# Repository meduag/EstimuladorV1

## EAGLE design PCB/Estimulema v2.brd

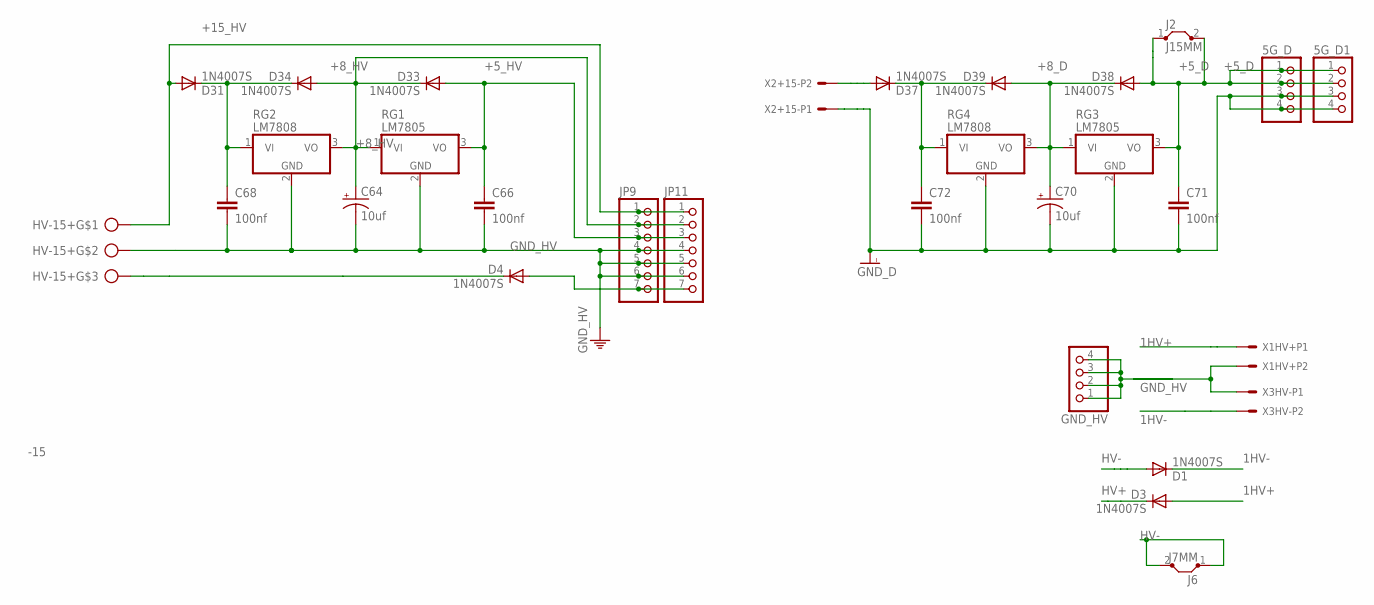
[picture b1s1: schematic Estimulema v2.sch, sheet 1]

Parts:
5G_D, 5G_D1: PINHD-1X4; 1X04
C64, C70: 10uf; E2-5
C66, C68, C71, C72: 100nf; C025-025X050
D1, D3, D4, D31, D33, D34, D37, D38, D39: 1N4007S; RESM4226X229
GND_HV: PINHD-1X4; 1X04
HV-15+: CONECTOR_3_PTR500; PTR_AK300/3
J2: J15MM; 15
J6: J7MM; 07
JP9, JP11: PINHD-1X7; 1X07
RG1, RG3: LM7805; TO220V
RG2, RG4: LM7808; TO220V
X1HV+, X2+15-, X3HV-: CONECTOR_5.08; CONECTOR_X2_5.08

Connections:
1HV+: D3.AN (A), X1HV+.1
1HV-: D1.CA (C), X3HV-.2
+5_D: 5G_D.1, 5G_D.2, 5G_D1.1, 5G_D1.2, C71.1, D38.AN (A), J2.1, J2.2, RG3.3 (VO); also elsewhere on the board
+5_HV: C66.1, D33.AN (A), JP9.3, JP11.3, RG1.3 (VO); also elsewhere on the board
+8_D: C70.+, D38.CA (C), D39.AN (A), RG3.1 (VI), RG4.3 (VO)
+8_HV: C64.+, D33.CA (C), D34.AN (A), JP9.2, JP11.2, RG1.1 (VI), RG2.3 (VO)
+15_HV: D31.AN (A), HV-15+.1, JP9.1, JP11.1; also elsewhere on the board
-15: D4.CA (C), HV-15+.3
-15_HV: D4.AN (A), JP9.7, JP11.7; also elsewhere on the board
GND_D: 5G_D.3, 5G_D.4, 5G_D1.3, 5G_D1.4, C70.-, C71.2, C72.2, RG3.2 (GND), RG4.2 (GND), X2+15-.1; also elsewhere on the board
GND_HV: C64.-, C66.2, C68.2, GND_HV.1, GND_HV.2, GND_HV.3, GND_HV.4, HV-15+.2, JP9.4, JP9.5, JP9.6, JP11.4, JP11.5, JP11.6, RG1.2 (GND), RG2.2 (GND), X1HV+.2, X3HV-.1; also elsewhere on the board
HV+: D3.CA (C); also elsewhere on the board
HV-: D1.AN (A), J6.1, J6.2; also elsewhere on the board
unnamed: D37.AN (A), X2+15-.2
unnamed: C68.1, D31.CA (C), D34.CA (C), RG2.1 (VI)
unnamed: C72.1, D37.CA (C), D39.CA (C), RG4.1 (VI)

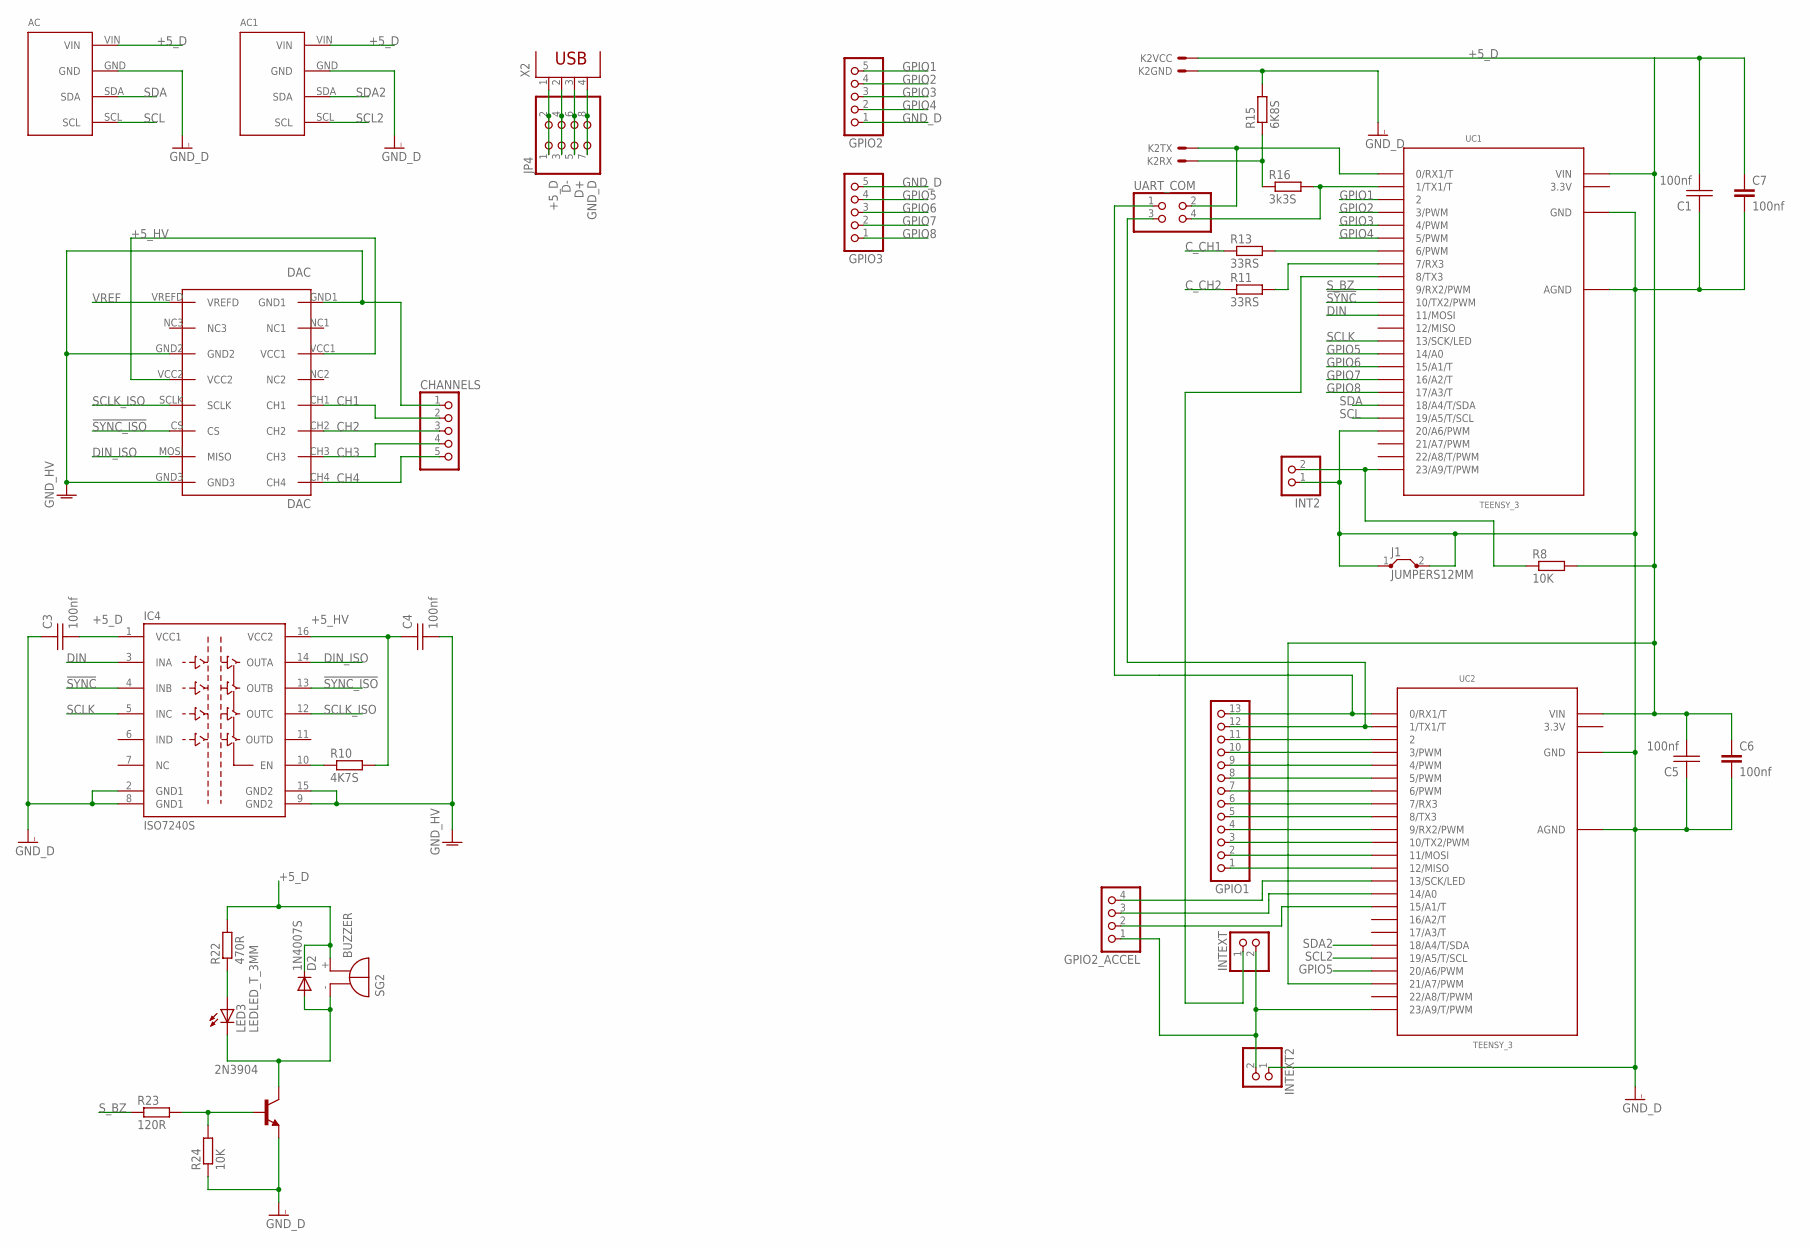
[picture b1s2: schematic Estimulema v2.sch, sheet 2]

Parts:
2N3904: 29-NPN-TO92-EBC; TO92-EBC
AC: CONECTOR_ACELEROMETRO_MPU6050CONECTOR_MPU6050; MPU6050
AC1: MPU6050
C1, C3, C4, C5: 100nf; CAP_CER_SMD-0805
C6, C7: 100nf; C025-025X050
CHANNELS: PINHD-1X5; 1X05
D2: 1N4007S; RESM4226X229
DAC: DAC; DACMOD_P
GPIO1: PINHD-1X13; 1X13
GPIO2, GPIO3: PINHD-1X5; 1X05
GPIO2_ACCEL: PINHD-1X4; 1X04
IC4: ISO7240S; SO-16DW
INT2: PINHD-1X2; 1X02
INTEXT, INTEXT2: PINHD-1X2; 1X02
J1: JUMPERS12MM; 12
JP4: PINHD-2X4; 2X04
K2: HC-06; CONECTOR_BTHC-06
LED3: LEDLED_T_3MM; LED3MM
R8, R24: 10K; RESISTENCIA_0805
R10: 4K7S; RESISTENCIA_0805
R11, R13: 33RS; RESISTENCIA_0805
R15: 6K8S; RESISTENCIA_0805
R16: 3k3S; RESISTENCIA_0805
R22: 470R; RESISTENCIA_0805
R23: 120R; RESISTENCIA_0805
SG2: BUZZER
UART_COM: PINHD-2X2; 2X02
UC1, UC2: TEENSY_3; TEENSY_3.0-3.2_DIL
X2: PN61729

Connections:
3.3V: UC1.3.3V, UC2.3.3V
!SYNC: IC4.4 (INB), UC1.10 (10/TX2/PWM)
!SYNC_ISO: DAC.CS, IC4.13 (OUTB)
+5_D: AC.VIN, AC1.VIN, C1.2, C3.2, C5.2, C6.1, C7.1, D2.CA (C), IC4.1 (VCC1), JP4.1, JP4.2, K2.1, R8.2, R22.2, SG2.+ (-), UC1.VIN, UC2.21/A7 (21/A7/PWM), UC2.VIN, X2.1; also elsewhere on the board
+5_HV: C4.1, DAC.VCC1, DAC.VCC2, IC4.16 (VCC2), R10.2; also elsewhere on the board
CH1: CHANNELS.2, DAC.CH1; also elsewhere on the board
CH2: CHANNELS.3, DAC.CH2; also elsewhere on the board
CH3: CHANNELS.4, DAC.CH3
CH4: CHANNELS.5, DAC.CH4
C_15D: GPIO1.11, UC2.2
C_CH1: R13.1; also elsewhere on the board
C_CH2: R11.1; also elsewhere on the board
D+: JP4.5, JP4.6, X2.3
D-: JP4.3, JP4.4, X2.2
DIN: IC4.3 (INA), UC1.11 (11/MOSI)
DIN_ISO: DAC.MOSI (MISO), IC4.14 (OUTA)
GND_D: 2N3904.E, AC.GND, AC1.GND, C1.1, C3.1, C5.1, C6.2, C7.2, GPIO2.1, GPIO3.5, IC4.2 (GND1), IC4.8 (GND1), INT2.1, INTEXT2.1, J1.1, J1.2, JP4.7, JP4.8, K2.2, R15.2, R24.1, UC1.20/A6 (20/A6/PWM), UC1.AGND, UC1.GND, UC2.AGND, UC2.GND, X2.4; also elsewhere on the board
GND_HV: C4.2, CHANNELS.1, DAC.GND1, DAC.GND2, DAC.GND3, IC4.9 (GND2), IC4.15 (GND2); also elsewhere on the board
GPIO1: GPIO2.5, UC1.2
GPIO2: GPIO2.4, UC1.3 (3/PWM)
GPIO3: GPIO2.3, UC1.4 (4/PWM)
GPIO4: GPIO2.2, UC1.5 (5/PWM)
GPIO5: GPIO3.4, UC1.14/A0, UC2.20/A6 (20/A6/PWM)
GPIO6: GPIO3.3, UC1.15/A1 (15/A1/T)
GPIO7: GPIO3.2, UC1.16/A2 (16/A2/T)
GPIO8: GPIO3.1, UC1.17/A3 (17/A3/T)
unnamed: GPIO2_ACCEL.1, INTEXT.2, INTEXT2.2, UC2.23/A9 (23/A9/T/PWM)
unnamed: INTEXT.1, UC1.8 (8/TX3)
unnamed: GPIO1.13, UART_COM.1, UC2.0 (0/RX1/T)
unnamed: GPIO1.12, UART_COM.3, UC2.1 (1/TX1/T)
unnamed: GPIO1.10, UC2.3 (3/PWM)
unnamed: GPIO1.9, UC2.4 (4/PWM)
unnamed: GPIO1.8, UC2.5 (5/PWM)
unnamed: GPIO1.7, UC2.6 (6/PWM)
unnamed: GPIO1.6, UC2.7 (7/RX3)
unnamed: GPIO1.5, UC2.8 (8/TX3)
unnamed: GPIO1.4, UC2.9 (9/RX2/PWM)
unnamed: GPIO1.3, UC2.10 (10/TX2/PWM)
unnamed: GPIO1.2, UC2.11 (11/MOSI)
unnamed: GPIO1.1, UC2.12 (12/MISO)
unnamed: R16.2, UART_COM.4, UC1.1 (1/TX1/T)
unnamed: GPIO2_ACCEL.4, UC2.13 (13/SCK/LED)
unnamed: K2.3, UART_COM.2, UC1.0 (0/RX1/T)
unnamed: GPIO2_ACCEL.3, UC2.14/A0
unnamed: GPIO2_ACCEL.2, UC2.15/A1 (15/A1/T)
unnamed: IC4.10 (EN), R10.1
unnamed: K2.4, R15.1, R16.1
unnamed: LED3.A, R22.1
unnamed: 2N3904.C, D2.AN (A), LED3.K (C), SG2.- (+)
unnamed: 2N3904.B, R23.2, R24.2
unnamed: INT2.2, R8.1, UC1.23/A9 (23/A9/T/PWM)
RL1: R13.2, UC1.6 (6/PWM)
RL2: R11.2, UC1.7 (7/RX3)
SCL: AC.SCL, UC1.19/A5 (19/A5/T/SCL)
SCL2: AC1.SCL, UC2.19/A5 (19/A5/T/SCL)
SCLK: IC4.5 (INC), UC1.13 (13/SCK/LED)
SCLK_ISO: DAC.SCLK, IC4.12 (OUTC)
SDA: AC.SDA, UC1.18/A4 (18/A4/T/SDA)
SDA2: AC1.SDA, UC2.18/A4 (18/A4/T/SDA)
S_BZ: R23.1, UC1.9 (9/RX2/PWM)
VREF: DAC.VREFD; also elsewhere on the board

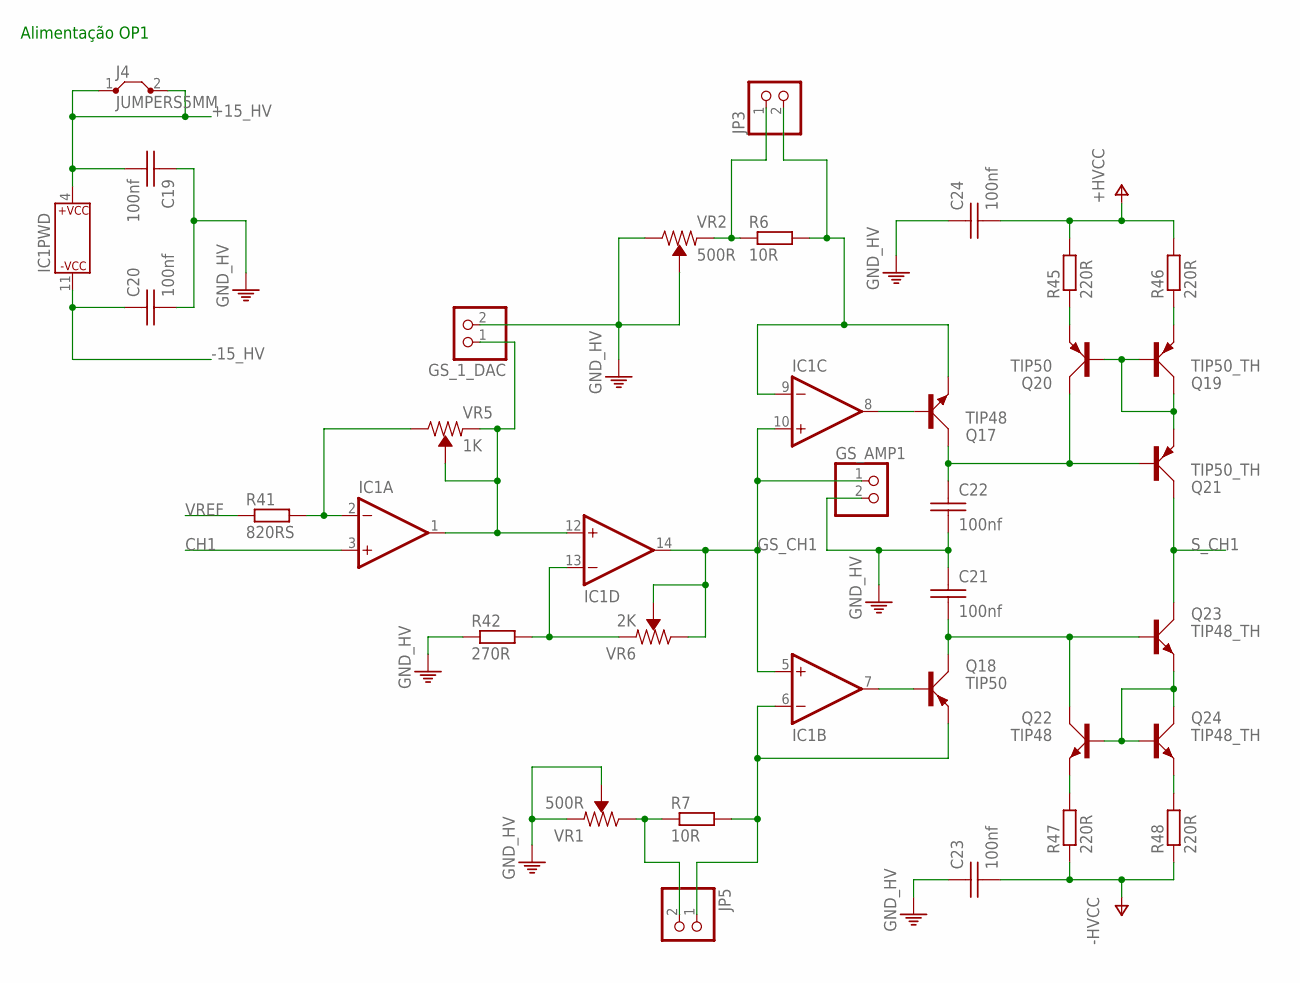
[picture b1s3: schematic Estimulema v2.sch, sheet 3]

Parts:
C19, C20: 100nf; CAP_CER_SMD-0805
C21, C22: 100nf; CAP_CER_2,54-5X5
C23, C24: 100nf; CAP_CER_16X7
GS_1_DAC: PINHD-1X2; 1X02
GS_AMP1: PINHD-1X2; 1X02
IC1: TL084DIL143D; DIL14
J4: JUMPERS5MM; 05
JP3, JP5: PINHD-1X2; 1X02
Q17, Q22: TIP48; TO220
Q18, Q20: TIP50; TO220
Q19, Q21: TIP50_TH; TO220
Q23, Q24: TIP48_TH; TO220
R6, R7: 10R; RESISTENCIA_0805
R41: 820RS; RESISTENCIA_0805
R42: 270R; RESISTENCIA_0805
R45, R46, R47, R48: 220R; 0204V
VR1, VR2: 500R; TRIMPOT-PTH-3386U
VR5: 1K; TRIMPOT-PTH-3386U
VR6: 2K; TRIMPOT-PTH-3386U

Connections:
+15_HV: C19.2, IC1.4 (P$V+), J4.1, J4.2; also elsewhere on the board
-15_HV: C20.1, IC1.11 (P$V-); also elsewhere on the board
CH1: IC1.3 (+IN); also elsewhere on the board
GND_HV: C19.1, C20.2, C21.1, C22.2, C23.1, C24.1, GS_1_DAC.2, GS_AMP1.2, R42.1, VR1.1 (CCW), VR1.2 (WIPER), VR2.2 (WIPER), VR2.3 (CW); also elsewhere on the board
GS_CH1: GS_AMP1.1, IC1.5 (+IN), IC1.10 (+IN), IC1.14 (OUT), VR6.2 (WIPER), VR6.3 (CW)
HV+: C24.2, R45.2, R46.2; also elsewhere on the board
HV-: C23.2, R47.1, R48.1; also elsewhere on the board
unnamed: JP5.2, R7.1, VR1.3 (CW)
unnamed: JP3.1, R6.1, VR2.1 (CCW)
unnamed: IC1.2 (-IN), R41.2, VR5.3 (CW)
unnamed: GS_1_DAC.1, IC1.1 (OUT), IC1.12 (+IN), VR5.1 (CCW), VR5.2 (WIPER)
unnamed: IC1.13 (-IN), R42.2, VR6.1 (CCW)
unnamed: IC1.9 (-IN), JP3.2, Q17.E, R6.2
unnamed: IC1.6 (-IN), JP5.1, Q18.E, R7.2
unnamed: C21.2, Q18.C, Q22.C, Q23.B
unnamed: C22.1, Q17.C, Q20.C, Q21.B
unnamed: Q20.E, R45.1
unnamed: Q19.E, R46.1
unnamed: Q19.B, Q19.C, Q20.B, Q21.E
unnamed: Q22.B, Q23.E, Q24.B, Q24.C
unnamed: Q22.E, R47.2
unnamed: Q24.E, R48.2
unnamed: IC1.8 (OUT), Q17.B
unnamed: IC1.7 (OUT), Q18.B
S_CH1: Q21.C, Q23.C; also elsewhere on the board
VREF: R41.1; also elsewhere on the board

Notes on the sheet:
Alimentação OP1

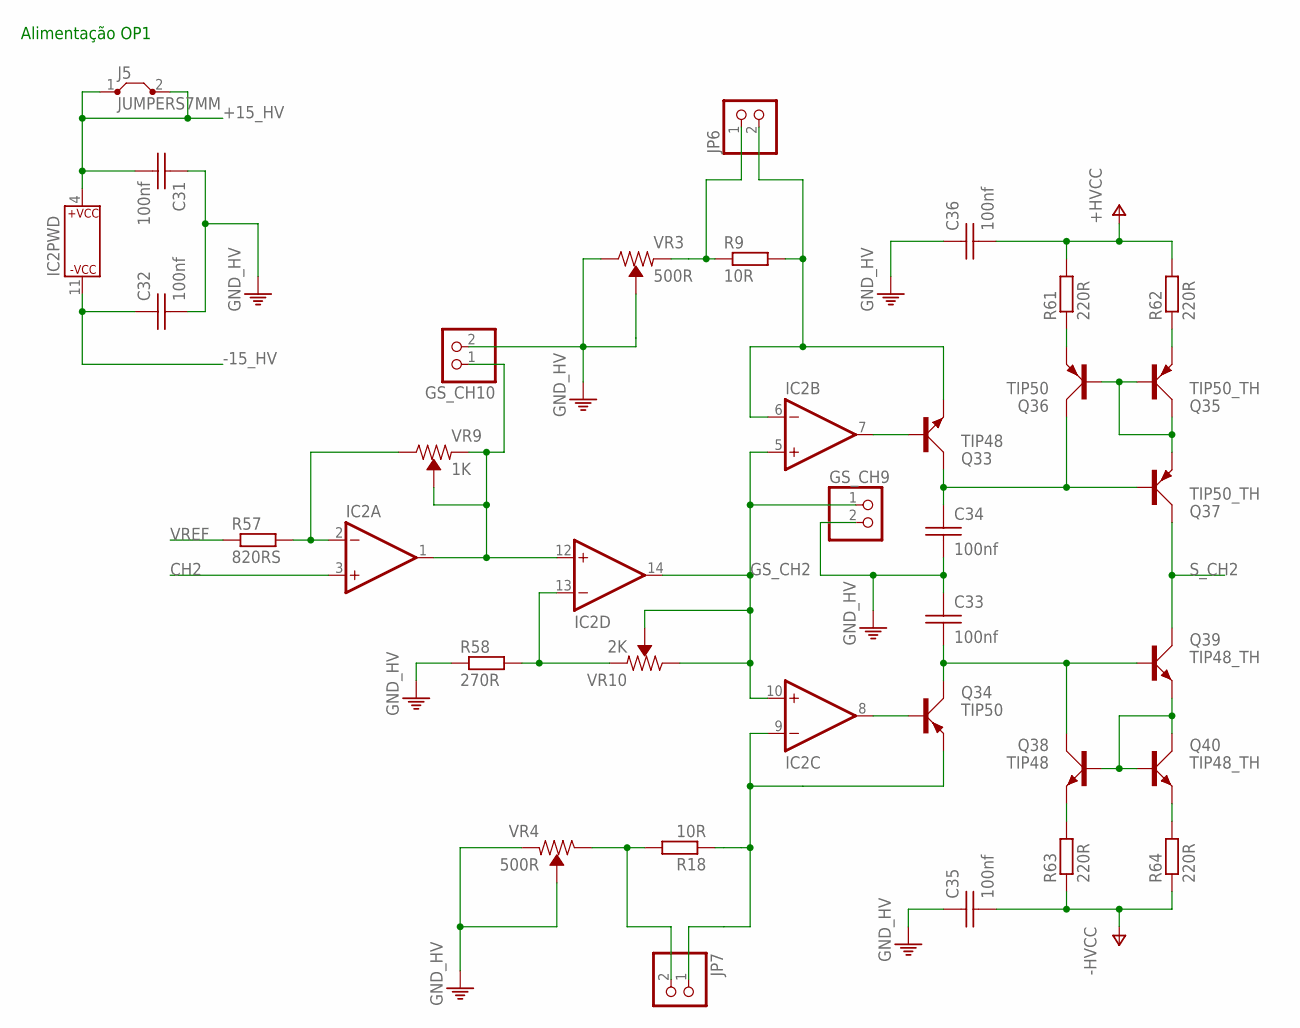
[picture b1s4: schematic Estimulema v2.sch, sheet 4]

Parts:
C31, C32: 100nf; CAP_CER_SMD-0805
C33, C34: 100nf; CAP_CER_2,54-5X5
C35, C36: 100nf; CAP_CER_16X7
GS_CH9, GS_CH10: PINHD-1X2; 1X02
IC2: TL084DIL143D; DIL14
J5: JUMPERS7MM; 07
JP6, JP7: PINHD-1X2; 1X02
Q33, Q38: TIP48; TO220
Q34, Q36: TIP50; TO220
Q35, Q37: TIP50_TH; TO220
Q39, Q40: TIP48_TH; TO220
R9, R18: 10R; RESISTENCIA_0805
R57: 820RS; RESISTENCIA_0805
R58: 270R; RESISTENCIA_0805
R61, R62, R63, R64: 220R; 0204V
VR3, VR4: 500R; TRIMPOT-PTH-3386U
VR9: 1K; TRIMPOT-PTH-3386U
VR10: 2K; TRIMPOT-PTH-3386U

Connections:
+15_HV: C31.2, IC2.4 (P$V+), J5.1, J5.2; also elsewhere on the board
-15_HV: C32.1, IC2.11 (P$V-); also elsewhere on the board
CH2: IC2.3 (+IN); also elsewhere on the board
GND_HV: C31.1, C32.2, C33.1, C34.2, C35.1, C36.1, GS_CH9.2, GS_CH10.2, R58.1, VR3.2 (WIPER), VR3.3 (CW), VR4.1 (CCW), VR4.2 (WIPER); also elsewhere on the board
GS_CH2: GS_CH9.1, IC2.5 (+IN), IC2.10 (+IN), IC2.14 (OUT), VR10.2 (WIPER), VR10.3 (CW)
HV+: C36.2, R61.2, R62.2; also elsewhere on the board
HV-: C35.2, R63.1, R64.1; also elsewhere on the board
unnamed: IC2.6 (-IN), JP6.2, Q33.E, R9.2
unnamed: JP6.1, R9.1, VR3.1 (CCW)
unnamed: JP7.2, R18.2, VR4.3 (CW)
unnamed: IC2.9 (-IN), JP7.1, Q34.E, R18.1
unnamed: IC2.2 (-IN), R57.2, VR9.3 (CW)
unnamed: GS_CH10.1, IC2.1 (OUT), IC2.12 (+IN), VR9.1 (CCW), VR9.2 (WIPER)
unnamed: IC2.13 (-IN), R58.2, VR10.1 (CCW)
unnamed: C33.2, Q34.C, Q38.C, Q39.B
unnamed: C34.1, Q33.C, Q36.C, Q37.B
unnamed: Q36.E, R61.1
unnamed: Q35.E, R62.1
unnamed: Q35.B, Q35.C, Q36.B, Q37.E
unnamed: Q38.B, Q39.E, Q40.B, Q40.C
unnamed: Q38.E, R63.2
unnamed: Q40.E, R64.2
unnamed: IC2.7 (OUT), Q33.B
unnamed: IC2.8 (OUT), Q34.B
S_CH2: Q37.C, Q39.C; also elsewhere on the board
VREF: R57.1; also elsewhere on the board

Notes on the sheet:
Alimentação OP1

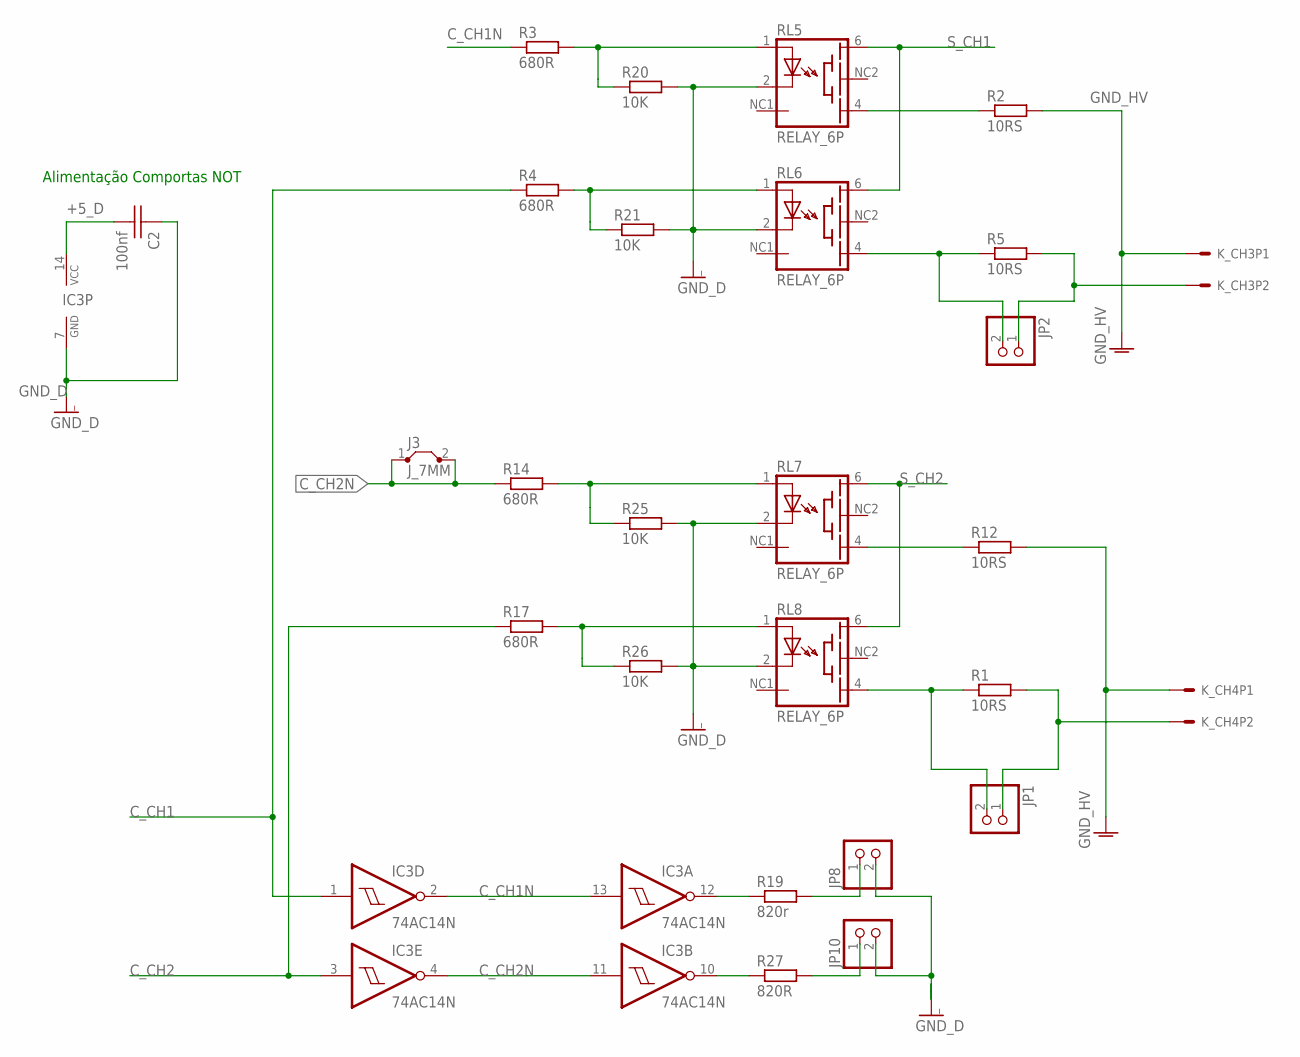
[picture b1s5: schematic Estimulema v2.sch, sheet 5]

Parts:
C2: 100nf; CAP_CER_SMD-0805
IC3: 74AC14N; DIL14
J3: J_7MM; 07
JP1, JP2, JP8, JP10: PINHD-1X2; 1X02
K_CH3, K_CH4: CONECTOR_5.08; CONECTOR_X2_5.08
R1, R5: 10RS; 0204/5
R2, R12: 10RS; 0617V
R3, R4, R14, R17: 680R; RESISTENCIA_0805
R19: 820r; RESISTENCIA_0805
R20, R21, R25, R26: 10K; RESISTENCIA_0805
R27: 820R; RESISTENCIA_0805
RL5, RL6, RL7, RL8: RELAY_6P; TS210

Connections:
+5_D: C2.2, IC3.14 (VCC); also elsewhere on the board
C_CH1: IC3.1 (I), R4.1; also elsewhere on the board
C_CH1N: IC3.2 (O), IC3.13 (I), R3.1
C_CH2: IC3.3 (I), R17.1; also elsewhere on the board
C_CH2N: IC3.4 (O), IC3.11 (I), J3.1, J3.2, R14.1
GND_D: C2.1, IC3.7 (GND), JP8.2, JP10.2, R20.2, R21.2, R25.2, R26.2, RL5.2 (C), RL6.2 (C), RL7.2 (C), RL8.2 (C); also elsewhere on the board
GND_HV: K_CH3.1, K_CH4.1, R2.2, R12.2; also elsewhere on the board
unnamed: R3.2, R20.1, RL5.1 (A)
unnamed: R4.2, R21.1, RL6.1 (A)
unnamed: R2.1, RL5.4 (EMI)
unnamed: JP2.2, R5.1, RL6.4 (EMI)
unnamed: R14.2, R25.1, RL7.1 (A)
unnamed: R17.2, R26.1, RL8.1 (A)
unnamed: R12.1, RL7.4 (EMI)
unnamed: JP2.1, K_CH3.2, R5.2
unnamed: JP1.1, K_CH4.2, R1.2
unnamed: JP1.2, R1.1, RL8.4 (EMI)
unnamed: JP8.1, R19.2
unnamed: IC3.12 (O), R19.1
unnamed: IC3.10 (O), R27.1
unnamed: JP10.1, R27.2
S_CH1: RL5.6 (BAS), RL6.6 (BAS); also elsewhere on the board
S_CH2: RL7.6 (BAS), RL8.6 (BAS); also elsewhere on the board

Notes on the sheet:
Alimentação Comportas NOT

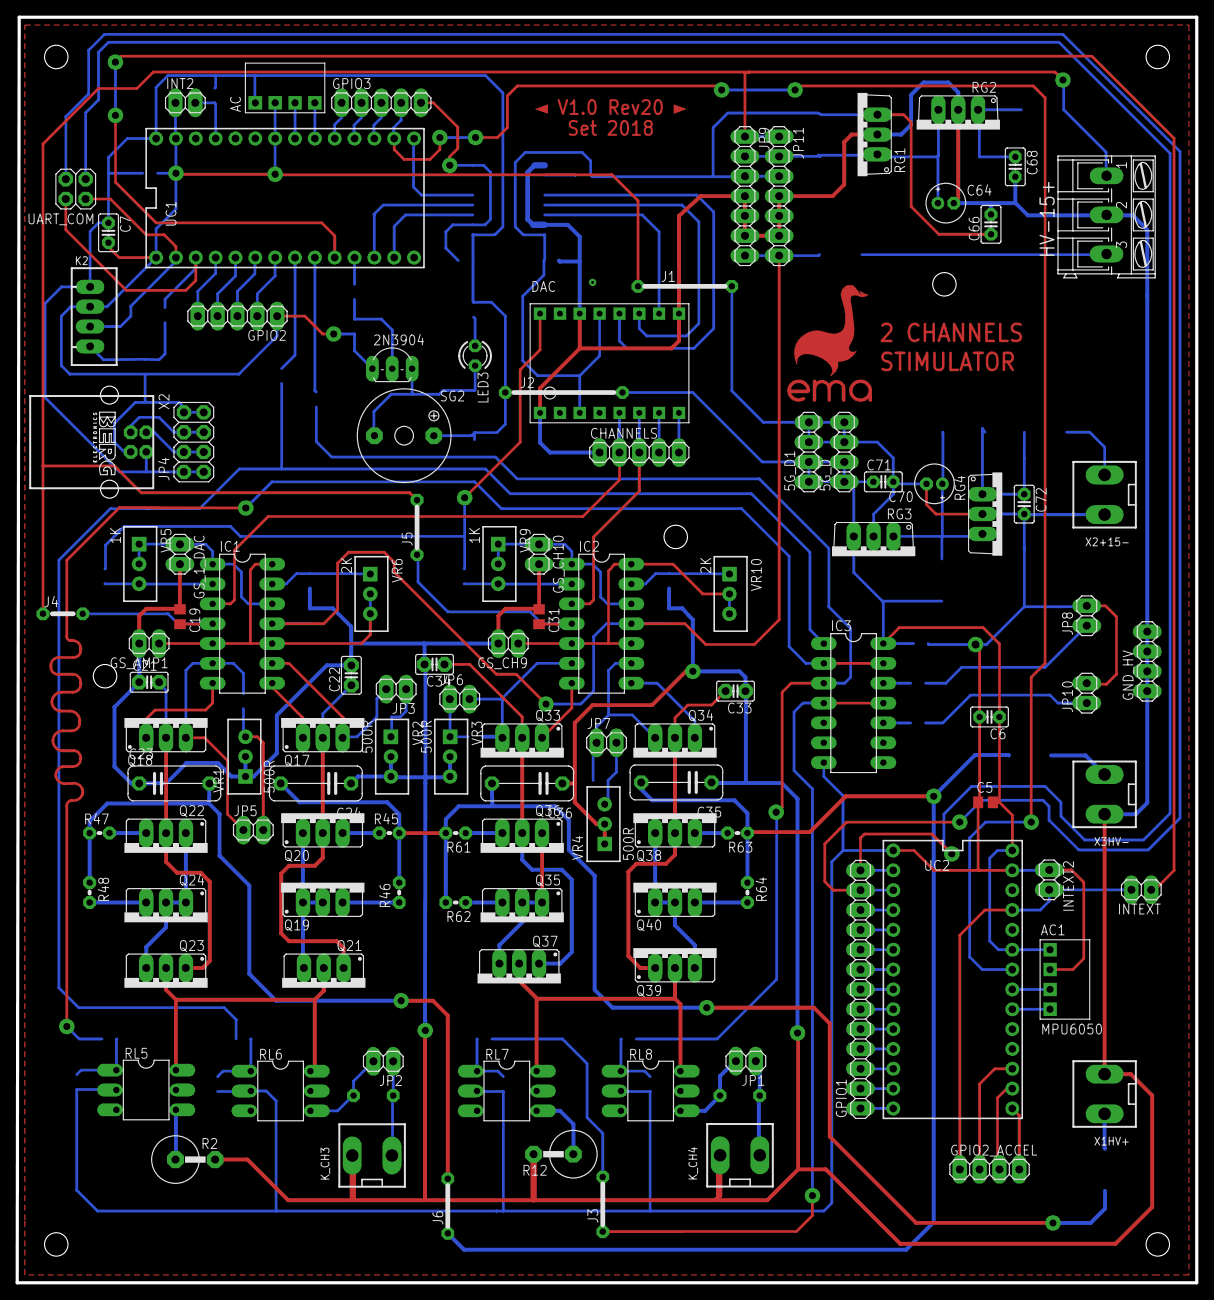
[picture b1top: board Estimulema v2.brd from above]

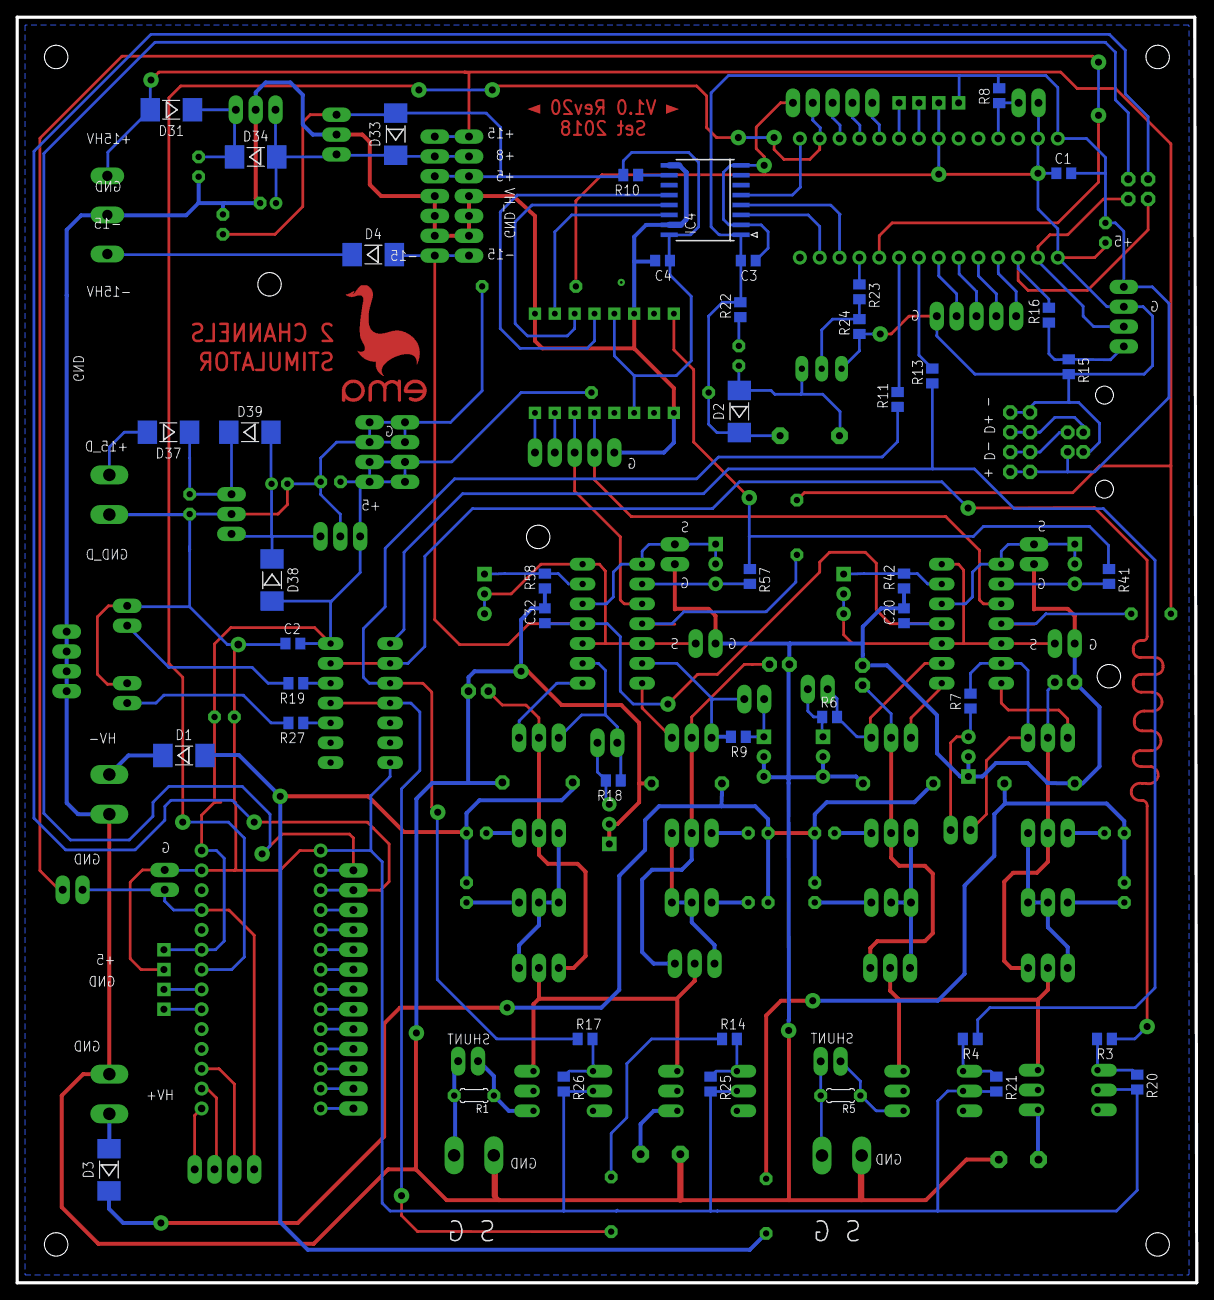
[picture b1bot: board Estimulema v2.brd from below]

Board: 2 copper layers, 151.0 x 162.0 mm, 159 parts (46 on the bottom side), 127 nets.

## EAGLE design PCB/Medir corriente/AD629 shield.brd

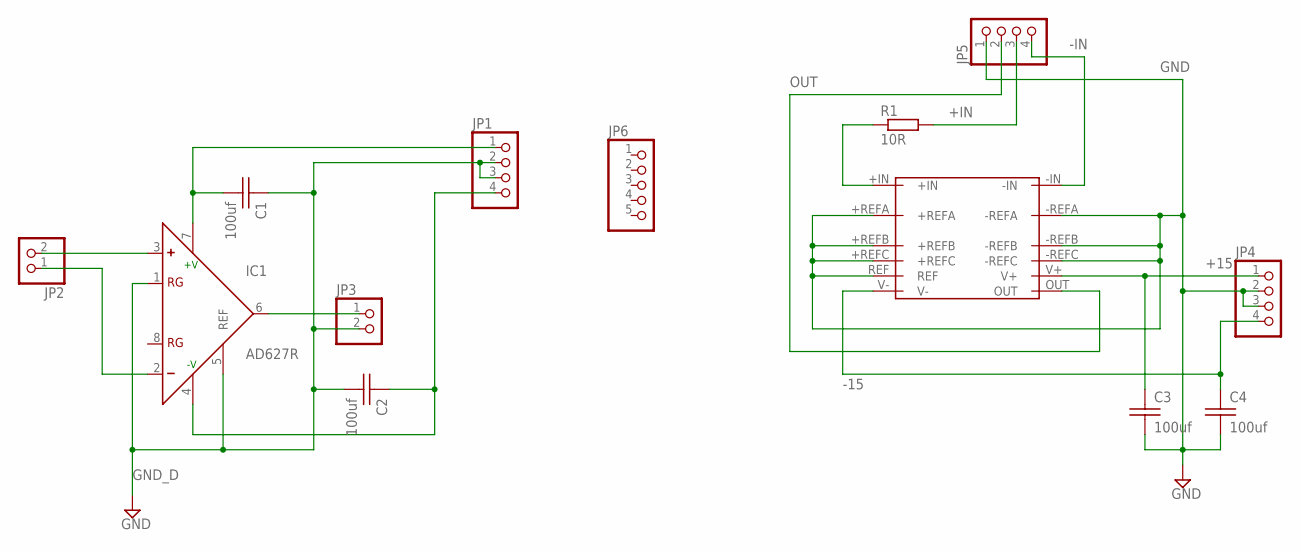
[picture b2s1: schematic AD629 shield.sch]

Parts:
C1, C2, C3, C4: 100uf; CAP_CER_SMD-0805
IC1: AD627R; SO8
JP1, JP4, JP5: PINHD-1X4; 1X04
JP2, JP3: PINHD-1X2; 1X02
JP6: PINHD-1X5; 1X05
R1: 10R; RESISTENCIA_0805
U$1: LT6375; LT6375_MS16(12)

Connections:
+15: C3.1, JP4.1, U$1.V+
+IN: JP5.3, R1.2
-15: C4.1, JP4.4, U$1.V-
-IN: JP5.4, U$1.-IN
GND: C3.2, C4.2, JP4.2, JP4.3, JP5.1, U$1.+REFA, U$1.+REFB, U$1.+REFC, U$1.-REFA, U$1.-REFB, U$1.-REFC, U$1.REF
GND_D: C1.1, C2.2, IC1.1 (RG), IC1.5 (REF), JP1.2, JP1.3, JP3.2
unnamed: IC1.3 (+), JP2.2
unnamed: IC1.2 (-), JP2.1
unnamed: C1.2, IC1.7 (+V), JP1.1
unnamed: C2.1, IC1.4 (-V), JP1.4
unnamed: IC1.6 (OUT), JP3.1
unnamed: R1.1, U$1.+IN
OUT: JP5.2, U$1.OUT

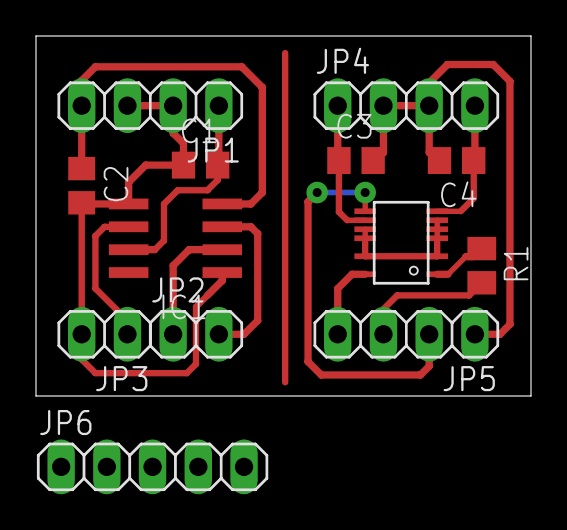
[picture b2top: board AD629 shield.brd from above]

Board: 2 copper layers, 27.5 x 20.0 mm, 13 parts (0 on the bottom side), 13 nets.

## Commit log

2019-03-07 Inicio final version end tese
    cosas para hacer en el link https://trello.com/c/CMSjg6Bh/17-estimulema
2019-03-08 const por define
2019-03-11 Fallos en la interface y control en el ino
    *- toca dividir por 10 el ton en el ino, en la interface ya esta corregido
    *- colocar na interface para teste tex
    *-
